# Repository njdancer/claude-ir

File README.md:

# claude-ir — ESP32 IR smart controller for ActronAir AC

A smart IR controller for an **ActronAir** (rebranded Midea) air conditioner.
The remote's IR protocol has been fully reverse-engineered, and a working
ESP8266 breadboard transmits real commands to the AC. The active mission is a
custom **ESP32-C3** dev board, taken from schematic → PCB → fabricated,
verified unit → production firmware → eventual HomeKit.

> 🤖 **Designed end-to-end by [Claude](https://claude.ai)** (Anthropic),
> directed by Nick Dancer. Reverse engineering, schematic, PCB layout,
> firmware, and the web UI were produced autonomously. Non-commercial hobby
> project.

📦 **Published board artifacts** (regenerated on every merge):
**<https://njdancer.github.io/claude-ir/>** — interactive 3D board viewer,
schematic PDF/SVGs, BOM, and the JLCPCB fabrication package.

## Status

| Part | State |
|------|-------|
| **IR protocol** | ✅ Reverse-engineered (BOSCH144 + COOLIX), documented in `re-findings.md` |
| **Breadboard POC** | ✅ Working — ESP8266 transmits to the real AC (the verified reference) |
| **ESP32-C3 board** | 🟢 v2 cost-down redesign — schematic + PCB complete, CI-green; **pre-fabrication** |
| **Firmware (ESP32-C3)** | 🟢 Ported (`pio run -e esp32-c3`); production hardening in progress |
| **Web control UI** | ✅ React Router app with mock + real serial |
| **HomeKit** | ⏸️ Not started |

See **[`ROADMAP.md`](./ROADMAP.md)** for the live project state and next
actions — it is the authoritative state file.

## Sources of truth

| Artifact | Truth for |
|----------|-----------|
| `hardware/*.kicad_sch` / `.kicad_pcb` | The board design (edit only via KiCad) |
| `hardware/esp32-ir-remote.net` | Reviewable electrical state (regenerated by `scripts/hardware-check.sh`) |
| `specs/hardware-dev-board-v1.md` | Board requirements (RFC-style spec) |
| `re-findings.md` | IR protocol knowledge (byte maps, timings) |
| `ROADMAP.md` | Project state & next actions |
| `hardware/notes/*.md` | Design rationale (if a note contradicts the schematic, the schematic wins) |

## The ESP32-C3 board (`hardware/`)

The custom board uses an **ESP32-C3-WROOM-02** module whose native
USB-Serial-JTAG controller means no USB-UART bridge chip: flash and monitor run
straight over USB-C. Key subsystems: 4× IR-emitter array (TSAL6200 via an
AO3400A driver), TSOP38238 IR receiver, AHT20 I²C temp/humidity sensor,
AMS1117-3.3 LDO from USB-C 5 V, and status/user LEDs. GPIO map and
per-subsystem rationale live in [`hardware/notes/README.md`](./hardware/notes/README.md).

**CI is the authoritative hardware gate** (`.github/workflows/ci.yml`): every PR
runs ERC/DRC vs `hardware/ci-baseline.json`, netlist freshness, schematic↔PCB
parity, page-extent and 3D-model checks, BOM LCSC lint, firmware builds + native
tests, and the app's typecheck/unit/e2e. Open a PR and watch CI rather than
re-running the battery by hand.

```bash
./scripts/hardware-check.sh              # ERC + regenerate netlist (needs kicad-cli)
python3 scripts/ci/hardware_validate.py  # full design gate (what CI runs)
python3 scripts/fab-outputs.py           # regenerate the JLCPCB order package
./scripts/build-site.sh                  # build the Pages site (schematic, 3D viewer, fab)
```

> ⚠️ KiCad work happens on Nick's Mac (KiCad 9 + the kicad MCP). Remote/web
> sessions do firmware, analysis, app, docs, and planning only — they queue
> KiCad tasks in `ROADMAP.md`.

## IR protocol

ActronAir is controlled with two protocols, both natively supported by
IRremoteESP8266:

- **BOSCH144** (144-bit) — climate state: power-on, temperature, mode, fan.
- **COOLIX** (24-bit) — discrete commands: power-off (`0xB27BE0`), swing, boost, LED.

The two payloads carry **disjoint** attributes, so AC state can be partially
stale after any single command — firmware must track per-payload freshness.
Full byte maps and timings are in [`re-findings.md`](./re-findings.md).

## Breadboard reference (working POC)

The proven ESP8266 reference that the board is based on:

- **Board:** ESP8266 NodeMCU (ESP-12E)
- **IR RX:** TSOP/VS1838B-class receiver OUT → GPIO14 (D5)
- **IR TX:** IR LED (940 nm) driven by a 2N2222 on GPIO4 (D2), 470 Ω base / current-limited LED

Full wiring is in [`wiring.md`](./wiring.md). The firmware exposes a 115200-baud
serial command interface:

| Command | Example | Description |
|---------|---------|-------------|
| `POWER:ON` / `POWER:OFF` | `POWER:ON` | On (BOSCH144) / Off (COOLIX) |
| `TEMP:<16.0–30.0>` | `TEMP:22.5` | Set temperature (0.5° steps) |
| `MODE:<COOL\|HEAT\|DRY\|FAN\|AUTO>` | `MODE:COOL` | Set mode |
| `FAN:<AUTO\|20…100>` | `FAN:60` | Set fan speed |
| `SWING` / `BOOST` / `LED` | `BOOST` | Special functions (COOLIX) |
| `STATE` | `STATE` | Query tracked state |

Responses are `OK:<message>` or `ERROR:<message>`.

## Web control UI (`app/`)

A React Router (v7) full-stack app for AC control over serial, with a mock
serial mode for hardware-free development.

```bash
cd app && pnpm install
MOCK_SERIAL=true pnpm dev   # http://localhost:5173, no hardware needed
pnpm test                   # vitest unit tests
pnpm test:e2e               # playwright e2e
```

For real hardware, set the serial port in `app/app/lib/serial.server.ts`.

## Build & test

```bash
pio run -e esp32-c3              # build the ESP32-C3 board firmware
pio run -e nodemcuv2             # build the ESP8266 breadboard firmware
pio test -e native              # host-side unit tests
./scripts/flash.sh              # flash from the macOS host
./scripts/monitor.sh            # serial monitor (115200)
python3 scripts/capture.py <lbl># capture one IR signal to captures/
python3 analysis/decoder.py     # analyze the capture corpus
```

Firmware builds run in the podman devcontainer (or host); flash/monitor run on
the macOS host (USB passthrough doesn't work under podman/macOS).

## References

- [IRremoteESP8266](https://github.com/crankyoldgit/IRremoteESP8266)
- [PlatformIO](https://docs.platformio.org/)
- [Claude Code on the web](https://code.claude.com/docs/en/claude-code-on-the-web)

## License

Non-commercial, educational/personal hobby project. The spark mark on the
published site is an original homage to Claude's logo.

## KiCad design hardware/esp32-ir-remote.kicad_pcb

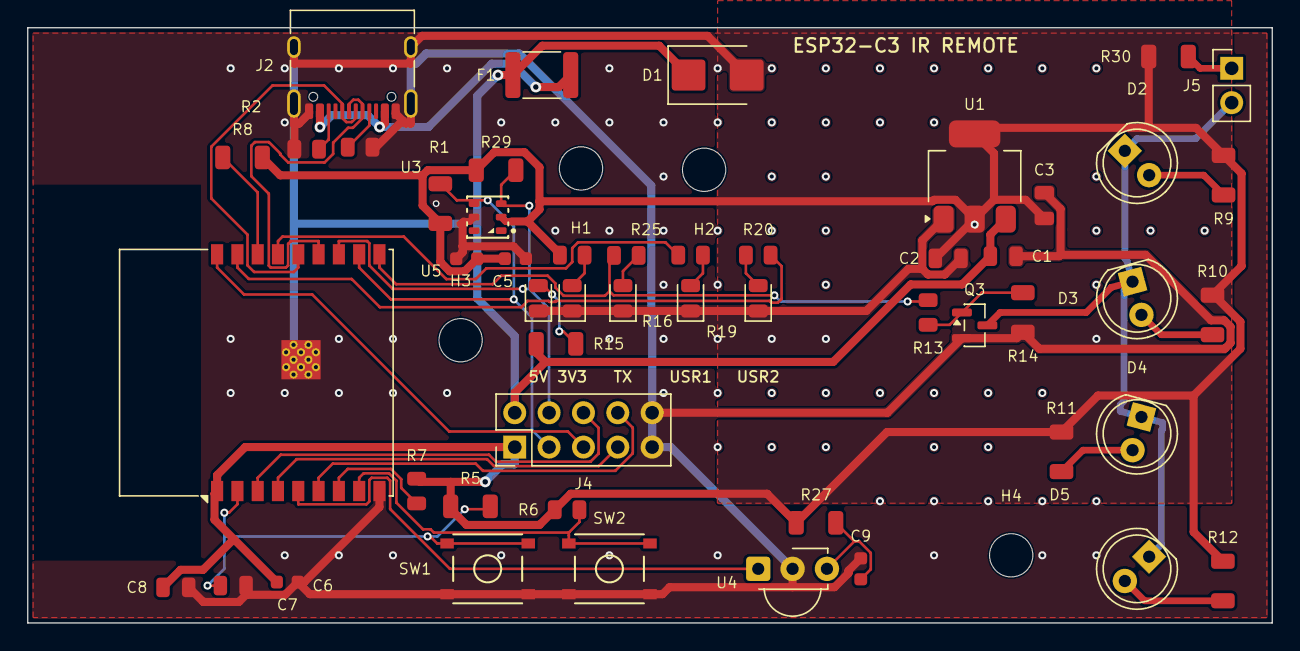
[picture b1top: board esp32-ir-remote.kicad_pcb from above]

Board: 2 copper layers, 92.0 x 44.0 mm, 55 parts (0 on the bottom side), 35 nets.

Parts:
C1, C8: 10µF; C_0805_2012Metric
C2, C3: 22µF; C_0805_2012Metric
C5, C7, C9: 100nF; C_0603_1608Metric
C6: 1µF; C_0805_2012Metric
C10: 10µF; C_0603_1608Metric
D1: D_TVS; D_SMB
D2, D3, D4, D5: TSAL6200; LED_D5.0mm
D6, D7, D10: Red; LED_0805_2012Metric
D11, D12: Yellow; LED_0805_2012Metric
F1: 1.1A; Fuse_1812_4532Metric
H1, H2, H3, H4: M3; MountingHole_3.2mm_M3
J2: USB_C_Receptacle_USB2.0_14P; USB_C_Receptacle_XKB_U262-16XN-4BVC11
J4: GPIO_PWR; PinHeader_2x05_P2.54mm_Vertical
J5: EXT_IR; PinHeader_1x02_P2.54mm_Vertical
Q3: AO3400A; SOT-23
R1, R2: 5.1kΩ; R_0805_2012Metric
R5: 10kΩ; R_1206_3216Metric
R6: 10kΩ; R_0805_2012Metric
R7: 10kΩ; R_0805_2012Metric
R8: 10kΩ; R_1206_3216Metric
R9, R10, R11, R12: 22Ω; R_1206_3216Metric
R13, R16, R19: 470Ω; R_0805_2012Metric
R14: 100kΩ; R_1206_3216Metric
R15: 1kΩ; R_1206_3216Metric
R20, R25: 1kΩ; R_0805_2012Metric
R27: 100Ω; R_1206_3216Metric
R28, R29: 4.7kΩ; R_1206_3216Metric
R30: 18Ω; R_1206_3216Metric
SW1: RESET; SW-SMD_TS-1187A-5.1x5.1
SW2: BOOT; SW-SMD_TS-1187A-5.1x5.1
U1: AMS1117-3.3; SOT-223-3_TabPin2
U3: ESP32-C3-WROOM-02
U4: TSOP382xx; Vishay_MINICAST-3Pin
U5: AHT20; SENSOR-SMD_L3.0-W3.0-P1.00-BR

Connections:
+3.3V: C2.1, C3.1, C5.2, C7.1, C8.1, C10.1, J4.1, R5.1, R6.1, R7.2, R8.2, R9.2, R10.2, R11.2, R12.2, R16.1, R27.1, R28.1, R29.1, R30.1, U1.2, U3.1, U5.2
+5V: C1.1, D1.1 (A1), F1.1, J4.2, R15.1, U1.3
/D11_A: D11.2, R25.2
/D12_A: D12.2, R20.1
/ESP_BOOT: R6.2, SW2.1, U3.8
/ESP_EN: C6.1, R5.2, SW1.1, U3.2
/EXT_IR_A: J5.1, R30.2
/I2C_SCL: J4.4, R29.2, U3.12, U5.3
/I2C_SDA: J4.3, R28.2, U3.11, U5.4
/IO2_STRAP: R8.1, U3.16
/IO8_STRAP: R7.1, U3.7
/IR_DRAIN: D2.1 (K), D3.1 (K), D4.1 (K), D5.1 (K), J5.2, Q3.3 (D)
/IR_RX: U3.5, U4.1 (OUT)
/IR_RX_VS: C9.1, R27.2, U4.3 (Vs)
/IR_TX: R13.2, R19.1, U3.10
/SPARE_IO0: J4.5, U3.18
/SPARE_IO1: J4.6, U3.3
/SPARE_RX: J4.7, U3.4
/SPARE_TX: J4.8, U3.6
/USB_D+: J2.A6, J2.B6, U3.14
/USB_D-: J2.A7, J2.B7, U3.13
/USER_LED1: R25.1, U3.15
/USER_LED2: R20.2, U3.17
GND: C1.2, C2.2, C3.2, C5.1, C6.2, C7.2, C8.2, C9.2, C10.2, D1.2 (A2), D6.1, D7.1, D10.1, D11.1, D12.1, J2.A1, J2.A12, J2.B1, J2.B12, J2.S1, J4.9, J4.10, Q3.2 (S), R1.2, R2.1, R14.1, SW1.2, SW2.2, U1.1, U3.9, U3.19, U4.2 (GND), U5.5
unnamed: D2.2 (A), R9.1
unnamed: D3.2 (A), R10.1
unnamed: D4.2 (A), R11.1
unnamed: D5.2 (A), R12.1
unnamed: D6.2, R15.2
unnamed: D7.2, R16.2
unnamed: D10.2, R19.2
unnamed: F1.2, J2.A4, J2.A9, J2.B4, J2.B9
unnamed: J2.A5, R1.1
unnamed: J2.B5, R2.2
unnamed: Q3.1 (G), R13.1, R14.2

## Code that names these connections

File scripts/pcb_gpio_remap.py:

#!/usr/bin/env python3
"""GPIO remap as a search dimension: reassign nets among U3's permutable pads.

Nick (2026-06-16) unlocked GPIO remapping ("I don't care what pins we use"). On
a 2-layer board, routability is dominated by *which module pad each net attaches
to* — a signal whose pad faces away from its peripheral zone forces a crossing.
The ESP32-C3 GPIO matrix lets almost any peripheral function sit on almost any
GPIO, so we can permute net->pad so each signal exits the side facing its zone.

This tool applies a permutation to the live .kicad_pcb (a cheap routability
probe). The placement re-seat (pcb_place_v2) is net-driven, so support parts
re-cluster against the new pad automatically. See hardware/notes/autoresearch.md.

A *winning* remap is reflected into the sources of truth separately (firmware
build_flags + schematic net reattach + netlist regen); this only probes.

Pad classes on U3 (ESP32-C3-WROOM-02), from the netlist:
  free   3(IO4) 4(IO5) 5(IO6) 6(IO7) 10(IO10) 15(IO3)  -- permute freely
  spare  11(IO20) 12(IO21) 17(IO1) 18(IO0)             -- permute (->J4 breakout)
  strap  7(IO8) 16(IO2)                                -- left fixed (boot levels)
  fixed  1 2 8 9 13 14 19                              -- power/EN/BOOT/GND/USB

  pcb_gpio_remap.py show                 # print current U3 pad->net
  pcb_gpio_remap.py apply gpio.json      # gpio.json = {"<pad>": "<net>", ...}
  pcb_gpio_remap.py pins gpio.json       # print the implied firmware GPIO map
"""
import json
import sys

import pcbnew

PCB = "hardware/esp32-ir-remote.kicad_pcb"

# pad -> GPIO number (for the firmware-pin readout); from the WROOM-02 pinout.
PAD_GPIO = {
    "1": "3V3", "2": "EN", "3": 4, "4": 5, "5": 6, "6": 7, "7": 8, "8": 9,
    "9": "GND", "10": 10, "11": 20, "12": 21, "13": 18, "14": 19, "15": 3,
    "16": 2, "17": 1, "18": 0, "19": "GND",
}
FREE = {"3", "4", "5", "6", "10", "15"}
SPARE = {"11", "12", "17", "18"}
PERMUTABLE = FREE | SPARE
FIXED = {"1", "2", "7", "8", "9", "13", "14", "16", "19"}

# nets that must never be moved off their hardware pad (belt-and-braces; these
# pads are in FIXED anyway, but guard by net name too).
LOCKED_NETS = {"/USB_D+", "/USB_D-", "+3.3V", "GND", "/ESP_EN", "/ESP_BOOT"}


def u3_pad_nets(board):
    """ref pad-number -> net name for U3."""
    for f in board.GetFootprints():
        if f.GetReference() == "U3":
            return {p.GetNumber(): p.GetNetname() for p in f.Pads()
                    if p.GetNumber().isdigit()}
    sys.exit("U3 not found")


def show(board=None):
    b = board or pcbnew.LoadBoard(PCB)
    nets = u3_pad_nets(b)
    print(f"{'pad':>4} {'gpio':>5} {'class':<6} net")
    for pad in sorted(nets, key=lambda p: int(p)):
        cls = ("free" if pad in FREE else "spare" if pad in SPARE
               else "fixed" if pad in FIXED else "?")
        print(f"{pad:>4} {str(PAD_GPIO.get(pad,'?')):>5} {cls:<6} {nets[pad]}")


def validate(board, gmap):
    """gmap = {pad: net}. Must be a permutation within the mentioned permutable
    pads: every target pad is permutable + unlocked, and the multiset of
    requested nets equals the multiset currently on exactly those pads."""
    cur = u3_pad_nets(board)
    pads = set(gmap)
    bad = pads - PERMUTABLE
    if bad:
        sys.exit(f"refuse: pads {sorted(bad)} are not permutable")
    locked = {p for p in pads if cur.get(p) in LOCKED_NETS}
    if locked:
        sys.exit(f"refuse: pads {sorted(locked)} carry locked nets")
    want = sorted(gmap.values())
    have = sorted(cur[p] for p in pads)
    if want != have:
        sys.exit(f"refuse: not a permutation within {sorted(pads)}\n"
                 f"  have {have}\n  want {want}")
    return cur


def apply(gmap, board=None, save=True):
    """Apply pad->net reassignment to U3. Returns the board."""
    b = board or pcbnew.LoadBoard(PCB)
    cur = validate(b, gmap)
    u3 = next(f for f in b.GetFootprints() if f.GetReference() == "U3")
    # resolve net objects once (FindNet by name)
    for pad in u3.Pads():
        n = pad.GetNumber()
        if n in gmap and gmap[n] != cur[n]:
            ni = b.FindNet(gmap[n])
            if ni is None:
                sys.exit(f"net {gmap[n]} not found on board")
            pad.SetNet(ni)
    if save:
        pcbnew.SaveBoard(PCB, b)
        changed = {p: gmap[p] for p in gmap if gmap[p] != cur[p]}
        print(f"remapped {len(changed)} U3 pads: {changed}")
    return b


def pins(gmap):
    """Print the firmware GPIO assignment implied by a remap (net -> GPIO#)."""
    b = pcbnew.LoadBoard(PCB)
    validate(b, gmap)
    cur = u3_pad_nets(b)
    merged = {**cur, **gmap}
    net_gpio = {merged[p]: PAD_GPIO[p] for p in merged}
    fw = {"/IR_TX": "IR_LED_PIN", "/IR_RX": "IR_RECV_PIN",
          "/I2C_SDA": "I2C_SDA_PIN", "/I2C_SCL": "I2C_SCL_PIN",
          "/USER_LED1": "USER_LED1_PIN", "/USER_LED2": "USER_LED2_PIN"}
    print("implied firmware pins (platformio.ini build_flags):")
    for net, macro in fw.items():
        if net in net_gpio:
            print(f"  -D {macro}={net_gpio[net]}")


if __name__ == "__main__":
    cmd = sys.argv[1] if len(sys.argv) > 1 else "show"
    if cmd == "show":
        show()
    elif cmd == "apply":
        apply({str(k): v for k, v in json.load(open(sys.argv[2])).items()})
    elif cmd == "pins":
        pins({str(k): v for k, v in json.load(open(sys.argv[2])).items()})
    else:
        sys.exit(__doc__)

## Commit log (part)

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2026-01-15 Add Circuit Schematic Viewer specification
    Draft specification for a web application that visualizes circuit.md
    files as interactive, filterable schematic diagrams. Key features:
    - Multi-file support with sub-circuit resolution
    - Four view modes: full, net-focused, component-focused, neighborhood
    - Search/filter panel with combinable filters
    - Basic validation (syntax, references, connectivity)
2026-01-15 Add layout module with force-directed positioning and Manhattan routing
    - Define layout types (Position, Vector, BoundingBox, PositionedNode, etc.)
    - Implement force-directed layout algorithm:
    - Node repulsion to prevent overlap
    - Edge attraction to keep connected nodes close
    - Temperature-based simulated annealing for convergence
    - Implement Manhattan (orthogonal) wire routing
2026-01-16 feat: Complete E2E tests for TEST-012 to TEST-017
    - Add neighborhood view filtering tests (TEST-015)
    - Add validation panel tests (TEST-017)
    - Fix test selectors to match actual implementations
    - All 28 E2E tests pass (with retries for flaky environment)
    Completes: TEST-012, TEST-013, TEST-014, TEST-015, TEST-016, TEST-017
2026-01-17 fix: prevent infinite loop in circuit processing useEffect
    The useEffect that processes circuit files was causing an infinite loop
    because it included project.loading and project.ast in its dependencies.
    When setAST was called during processing, the dependency change triggered
    the effect again, and the guard condition didn't prevent re-entry.
    Fix: Use a ref to track which content we've started processing, preventing
    the effect from re-running for the same content.
2026-06-10 H1.4 datasheet review: board electrically sound; fix datasheet files
    6 parallel subagents (one per subsystem) re-derived required connections from
    datasheets and diffed against the netlist; every ERROR/HIGH item was re-verified
    against the netlist directly. Result: the design is electrically sound. Full
    record in hardware/notes/datasheet-review-h1.4.md.
    Verified clean: AP63203 power (pinout/BST/caps/EN), USB-C protection ordering
    (fuse before TVS), CH340C (V3/VCC@3.3V, R232 grounded, USB routing, CC Rd
2026-06-10 ROADMAP: kicad-edit MCP smoke-tested (reads + render work; KiCad 9 needs explicit layers for board view)
2026-06-10 v1.2 wrap-up: regenerate BOM from schematic, demote BOM.md, roadmap
    BOM CSV regenerated with DNP column; only the 3 hand-solder pin headers
    lack LCSC (deliberate). Restored LCSC on the 8 symbol-swapped parts (the
    replace tool drops custom fields) and fixed two more latent code bugs
    found while re-verifying every code on LCSC/JLCPCB: Q3 IRLML6344 carried
    C8545 (the 2N7002 code) -> C53550; R14 100k and R15 1k carried 0805 codes
    on 1206 footprints -> C17900 / C4410 (both Basic, >900k stock).
2026-06-10 H2.2: board outline 80x55 + full placement, zero courtyard overlaps
    - Outline (100,60)-(180,115) with 4x M3 NPTH mounting holes (H1 pulled east
    of the WROOM antenna courtyard wedge; H3/H4 in corners)
    - All 76 footprints placed per hardware/notes/layout.md zones:
    WROOM antenna overhangs west edge 1.5mm; IR fan D2-D5 north edge rotated
    -67.5/-22.5/+22.5/+67.5 with R9-R12 row behind; TSOP+RC NE corner facing
    east; DHT22 + Qwiic + spare header east; USB-C south-center (mouth
2026-06-10 H2.3: zero splits again - all nets connected (probed-lane hand routes)
2026-06-11 H3.1: JLCPCB fab outputs - gerbers.zip, BOM (35 lines, DNP excluded), CPL (67 placements)
    + board renders (top/bottom/iso) staged in fab/; site script render flags fixed
2026-06-11 Site: Claude attribution + cache-busted viewer assets
    - 'designed by Claude' spark badge on index + viewer header, attribution
    footer (original SVG homage to the Claude starburst in terracotta
    #D97757 - no redistributed brand assets; non-commercial hobby project)
    - board.glb and layer SVGs now load with ?v=<commit> so browsers re-fetch
    after every deploy (the bare-board GLB Nick saw was a stale browser
    cache of the pre-model-fix file)
2026-06-11 Viewer: real per-face STEP colors via KiCad 10 CI image
    KiCad 9 Linux builds drop STEP model colors in GLB export, which is why
    every component rendered as one flat hand-picked color. KiCad 10.0.2
    exports them correctly (verified in-container on the real board: 0
    material-less primitives, 24 component materials vs 0).
    - pages.yml: kicad/kicad:9.0.6 -> 10.0.2; drop nodesource (trixie ships
    node 20, enough for gltf-transform)
2026-06-13 3D models: vendor TS-1187A STEP; fix AM2302 seating (Nick's review)
    Nick's render review caught both:
    - SW1/SW2 had no 3D model since the v1.4 footprint swap. EasyEDA STEP
    for TS-1187A-B-A-B vendored to hardware/lib/3dshapes/ (KIPRJMOD-
    relative, per the CI-renders rule) and referenced from the library
    footprint + both board instances at offset 0 - terminal positions in
    the model (x +/-3.0, y +/-1.85) verified against the footprint pads
2026-06-13 ROADMAP: correct AM2302 model-seating claim (fix didn't persist)
    The earlier 'AM2302 re-seated' note was wrong: the pcbnew Python offset
    edit hit a SWIG value-copy gotcha (m_Offset returned by value, so the
    assignment was discarded) and the committed offset is still y -0.7. The
    AM2302.step model also carries internal STEP placement transforms that
    headless geometry parsing can't resolve, so the correct offset can't be
    determined here. Copper/footprint are fine (cosmetic 3D-viewer only);
2026-06-13 ROADMAP: flip USB-C back to SMD 16P (cheaper at 5-board min)
    At the 5-board minimum the THT part premium ($1.42x5=$7.10) exceeds the
    one-time SMD feeder ($0.065x5+$3=$3.33) by ~$3.77, and SMD needs no
    hand-soldering. 16P SMD has through-hole mounting posts for strength. Feeders
    back to 4 (C3 + AHT20 + buck + USB-C); per-board parts ~$7.3 (-55% vs v1.4).
    USB-C leaves the hand-solder kit.
2026-06-13 wip(sch): snap new symbols to grid (fixes 44 off-grid ERC) + cleanup script
2026-06-14 wip(pcb): clean rip→place→route→heal→pour pipeline + placement fix
    - pcb_place_v2.py: collision-checked placer re-seats C3-support parts at
    nearest free slot to their pin (closed IO8_STRAP + I2C_SDA, 7→4 unrouted)
    - pcb_stub_heal.py: root-caused the THT-pad shortfall (router targets pad
    bbox, round-pad corners are outside copper); vertex-anchored bridge with
    foreign-clearance guard. No shorts; refuses bridges that would short.
    - 8 unconnected remaining, all characterised: 3 = THT USB-C escape (→SMD
2026-06-14 silk: auto-place refs + strip passive outlines (overlap 85->35)
    Rewrote pcb_silk.py: strips R*/C* passive silk outlines (CPL-placed, the
    outline buys nothing) + stale v1 board labels, then auto-places every
    reference (0.8mm = silk min) at the nearest spot clear of pads/courtyards/
    other refs. Phases run in separate processes (LoadBoard-after-Remove curse).
    Result: silk_overlap 85->35 (<=44 baseline), silk_edge 6->2, text_height
    fixed, 0 refs hidden. silk_over_copper 50 (cosmetic, mask-isolated; denser v2
2026-06-14 fix(pcb): rotate J2 USB-C 3D model 180° (Z) to match footprint orientation
    The vendored C393939 (EasyEDA-derived) STEP for the XKB U262 receptacle faced
    the wrong way on KiCad's native footprint. Apply (rotate (xyz 0 0 180)) in the
    model block. Model/visual-only — no change to pads, nets, or geometry. Offset
    still to be confirmed visually once rotated.
    https://claude.ai/code/session_015Dv9tDv1tdc4f4CRZuxPSM
2026-06-14 docs: add persevere-on-long-tasks principle + phase the board restructure
    CLAUDE.md: new principle — don't stall/self-truncate on long jobs, commit
    AND push each increment (pre-authorised on the working branch), delegate
    parallel sub-tasks to subagents, rely on auto-compact rather than cutting
    scope. ROADMAP: phase the restructure (A outline+anchors, B support
    re-seat, C route/pour/silk, C2 underside metadata, D validate/CI, E
    schematic split last/GUI-bound). Records that the Claude spark is 8 F.SilkS
2026-06-14 fix(pcb): real DRC fixes + baseline refresh for the restructured board
    - hole_to_hole: pour stitching now respects drill-to-drill spacing vs every
    PTH pad (a GND via had landed 0.54mm from U4's GND through-hole pad).
    - text_height: bumped all silk labels/metadata to the 0.8mm minimum.
    - 3D model path: ENV is hardware/, so ${KIPRJMOD}/hardware/... doubled the
    path; bent-LED model now ${KIPRJMOD}/lib/3dshapes/... and resolves.
    - Refreshed hardware/ci-baseline.json for the legitimately-changed counts
2026-06-14 fix(pcb): silk legibility — hide LCSC part-codes, fix overlaps + logo
    The front silk was illegible: the BOM workflow left every footprint's LCSC
    part-number field visible on F.SilkS at full 1.27mm, so 25 part codes piled
    on top of the reference designators.
    pcb_silk.py changes:
    - hide ALL footprint fields except Reference (not just Value) -> removes the
    25 stray LCSC codes
2026-06-14 fix(pcb): declutter U4 silk ref to clear D11 (CI silk_overlap 46->44)
    The U4 relocation left its reference designator auto-placed at
    (155.045, 106.105), overlapping D11's ref field + silkscreen — the only
    hard CI failure (hardware job: silk_overlap warning count 44 -> 46, which
    the baseline gates on increase). Moved the U4 ref into the clear gap east
    of the part (158.5, 110.0), between U4 and U5 and south of the D12 silk.
    Silk-only change (no re-route). DRC now matches baseline: silk_overlap 44,
2026-06-14 renders for PR #23 @ 7b0900fe30177424da9dee53e1995b081d22f4f9
2026-06-15 wip(pcb): LDO thermal — rot90 tab-north + to-the-edge GND-replacing pour
    Placement/pour progress (board regenerated from these by the pipeline; not
    committed while the autorouter is being reworked):
    - U1 rot90 so the SOT-223 tab faces NORTH into the pour (max heat spread,
    per Nick); nudged to (120,80.5) to clear F1's courtyard.
    - pcb_ldo_pour.py: F.Cu pour now runs to the N+W board edges and DISPLACES
    GND in the corner instead of carving a high-priority island out of it
2026-06-15 renders for PR #24 @ 2c7befddcef8dc2074a45082d5f94492f055f119
2026-06-15 feat(ci): KiBot owns the ERC/DRC error gate; kill the warning-count drift
    Two changes that finish the gate consolidation:
    - KiBot's erc/drc preflights now GATE in CI (dropped `-s erc,drc`) — they fail
    on real ERC/DRC errors, version-independently. Verified the clean board still
    exits 0 (the 1 benign lib_symbol_mismatch ERC warning doesn't fail).
    - hardware_validate.py: WARNING-severity baseline count changes
    (lib_footprint_mismatch, silk_edge_clearance, lib_symbol_mismatch) are now
2026-06-15 ci/kibot: add zone-fill check, parity/silk filters, KiDiff PR visual diff
    KiBot quick wins:
    - check_zone_fills preflight — fails if any copper zone's fill is stale vs
    the board (our pour -> ldo_pour pipeline could otherwise ship a stale fill).
    - DRC filters for the two genuinely-benign warning classes: board-only
    mounting-hole/logo extra_footprint (H1-H4, REF**, never in the netlist)
    and the inherent J2 USB-C silk-vs-edge clip. Real parity mismatches are
2026-06-15 docs(hw): reconcile cap/sensor notes to v2; audit decoupling banks
    Audited all nine caps after Nick's "are C7/C8 and C5/C10 duplicated?"
    question. Verdict: not a copy-paste bug — within each pair the 100 nF
    (HF) and 10 µF (bulk) do different jobs, and the two identical banks
    exist because the +3.3V rail has two consumers (U3 the C3 module, U5
    the AHT20), i.e. one bank per IC. There is no C4 (deleted with the
    CH340C in v2).
2026-06-15 hw: floorplan-search findings + USB-keepout probe (item 2)
    Generative search (N=40) verdict: the merged 2-layer floorplan is already
    near-optimal. Only 3/40 candidates were DRC-legal; the best beats baseline by
    ~3% (LDO tucked into the NW corner) — within run-to-run jitter noise, so the
    board is left unchanged rather than churned for a marginal, noisy gain. Nick's
    "everything bottom-left + J4 under the ESP" hypothesis routed worse/illegal.
    Item 2 (USB -> F.Cu): pcb_usb_keepout.py adds a B.Cu keepout under the J2->U3
2026-06-16 renders for PR #28 @ b6e1071c801288f4c972b1a694fae0f94e84bf1f
